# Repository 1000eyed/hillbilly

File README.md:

# hillbilly
This a work in progress repository of a hillbilly keyboard.

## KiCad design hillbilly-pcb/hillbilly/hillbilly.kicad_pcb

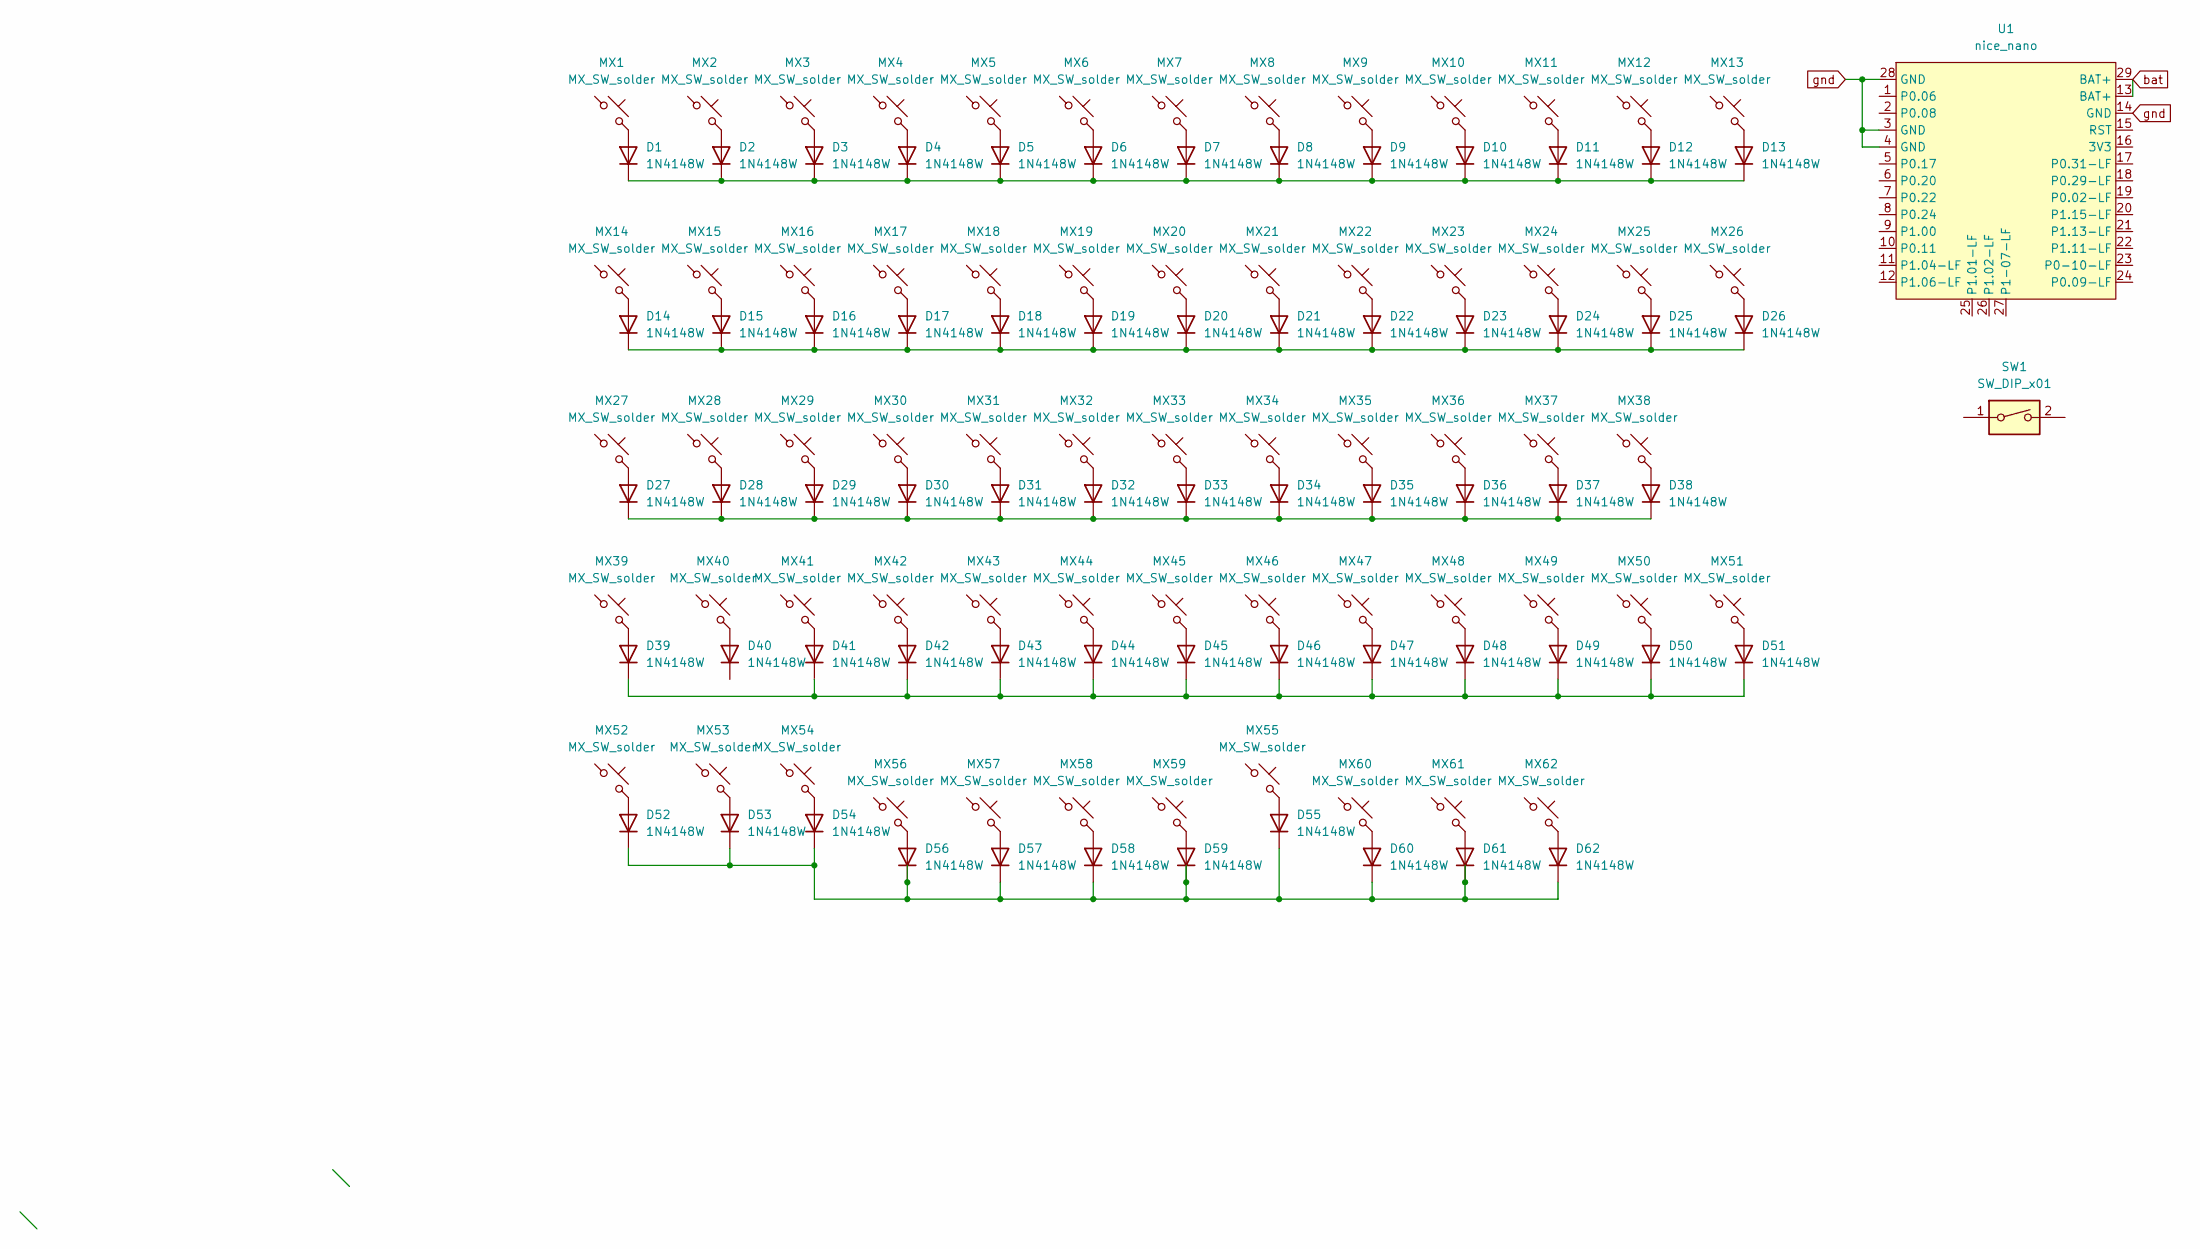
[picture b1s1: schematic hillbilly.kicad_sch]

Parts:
D1, D2, D3, D4, D5, D6, D7, D8, D9, D10, D11, D12, D13, D14, D15, D16, D17, D18, D19, D20, D21, D22, D23, D24, D25, D26, D27, D28, D29, D30, D31, D32, D33, D34, D35, D36, D37, D38, D39, D40, D41, D42, D43, D44, D45, D46, D47, D48, D49, D50, D51, D52, D53, D54, D55, D56, D57, D58, D59, D60, D61, D62: 1N4148W; D_SOD-123
MX1, MX2, MX3, MX4, MX5, MX6, MX7, MX8, MX9, MX10, MX11, MX15, MX16, MX17, MX18, MX19, MX20, MX21, MX22, MX23, MX24, MX28, MX29, MX30, MX31, MX32, MX33, MX34, MX35, MX36, MX37, MX40, MX41, MX42, MX43, MX44, MX45, MX46, MX47, MX48, MX49, MX50, MX51, MX56, MX59, MX60, MX61, MX62: MX_SW_solder; SW_MX_HS_1u
MX12: MX_SW_solder; SW_MX_1u_1.5u_2u
MX13, MX26: MX_SW_solder; SW_MX_1u
MX14: MX_SW_solder; SW_MX_HS_1.5u
MX25: MX_SW_solder; SW_MX_1u_2u_ISO
MX27: MX_SW_solder; SW_MX_HS_1.75u+1.25u_stepped_caps
MX38: MX_SW_solder; SW_MX_HS_1.75u
MX39: MX_SW_solder; SW_MX_HS_1u_2u
MX52, MX53, MX54, MX55: MX_SW_solder; SW_MX_HS_1.25u
MX57: MX_SW_solder; SW_MX_HS_2.75u_1.75u
MX58: MX_SW_solder; SW_MX_HS_1.75u_2.75u
SW1: SW_DIP_x01
U1: nice_nano; nice_nano_AH_USBup

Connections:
unnamed: D1.2 (A), MX1.2
unnamed: D1.1 (K), D2.1 (K), D3.1 (K), D4.1 (K), D5.1 (K), D6.1 (K), D7.1 (K), D8.1 (K), D9.1 (K), D10.1 (K), D11.1 (K), D12.1 (K), D13.1 (K)
unnamed: D2.2 (A), MX2.2
unnamed: D3.2 (A), MX3.2
unnamed: D4.2 (A), MX4.2
unnamed: D5.2 (A), MX5.2
unnamed: D6.2 (A), MX6.2
unnamed: D7.2 (A), MX7.2
unnamed: D8.2 (A), MX8.2
unnamed: D9.2 (A), MX9.2
unnamed: D10.2 (A), MX10.2
unnamed: D11.2 (A), MX11.2
unnamed: D12.2 (A), MX12.2
unnamed: D13.2 (A), MX13.2
unnamed: D14.2 (A), MX14.2
unnamed: D14.1 (K), D15.1 (K), D16.1 (K), D17.1 (K), D18.1 (K), D19.1 (K), D20.1 (K), D21.1 (K), D22.1 (K), D23.1 (K), D24.1 (K), D25.1 (K), D26.1 (K)
unnamed: D15.2 (A), MX15.2
unnamed: D16.2 (A), MX16.2
unnamed: D17.2 (A), MX17.2
unnamed: D18.2 (A), MX18.2
unnamed: D19.2 (A), MX19.2
unnamed: D20.2 (A), MX20.2
unnamed: D21.2 (A), MX21.2
unnamed: D22.2 (A), MX22.2
unnamed: D23.2 (A), MX23.2
unnamed: D24.2 (A), MX24.2
unnamed: D25.2 (A), MX25.2
unnamed: D26.2 (A), MX26.2
unnamed: D27.2 (A), MX27.2
unnamed: D27.1 (K), D28.1 (K), D29.1 (K), D30.1 (K), D31.1 (K), D32.1 (K), D33.1 (K), D34.1 (K), D35.1 (K), D36.1 (K), D37.1 (K), D38.1 (K)
unnamed: D28.2 (A), MX28.2
unnamed: D29.2 (A), MX29.2
unnamed: D30.2 (A), MX30.2
unnamed: D31.2 (A), MX31.2
unnamed: D32.2 (A), MX32.2
unnamed: D33.2 (A), MX33.2
unnamed: D34.2 (A), MX34.2
unnamed: D35.2 (A), MX35.2
unnamed: D36.2 (A), MX36.2
unnamed: D37.2 (A), MX37.2
unnamed: D38.2 (A), MX38.2
unnamed: D39.2 (A), MX39.2
unnamed: D39.1 (K), D41.1 (K), D42.1 (K), D43.1 (K), D44.1 (K), D45.1 (K), D46.1 (K), D47.1 (K), D48.1 (K), D49.1 (K), D50.1 (K), D51.1 (K)
unnamed: D40.2 (A), MX40.2
unnamed: D41.2 (A), MX41.2
unnamed: D42.2 (A), MX42.2
unnamed: D43.2 (A), MX43.2
unnamed: D44.2 (A), MX44.2
unnamed: D45.2 (A), MX45.2
unnamed: D46.2 (A), MX46.2
unnamed: D47.2 (A), MX47.2
unnamed: D48.2 (A), MX48.2
unnamed: D49.2 (A), MX49.2
unnamed: D50.2 (A), MX50.2
unnamed: D51.2 (A), MX51.2
unnamed: D52.2 (A), MX52.2
unnamed: D52.1 (K), D53.1 (K), D54.1 (K), D55.1 (K), D56.1 (K), D57.1 (K), D58.1 (K), D59.1 (K), D60.1 (K), D61.1 (K), D62.1 (K)
unnamed: D53.2 (A), MX53.2
unnamed: D54.2 (A), MX54.2
unnamed: D55.2 (A), MX55.2
unnamed: D56.2 (A), MX56.2
unnamed: D57.2 (A), MX57.2
unnamed: D58.2 (A), MX58.2
unnamed: D59.2 (A), MX59.2
unnamed: D60.2 (A), MX60.2
unnamed: D61.2 (A), MX61.2
unnamed: D62.2 (A), MX62.2
bat: U1.13 (BAT+), U1.29 (BAT+)
gnd: U1.3 (GND), U1.4 (GND), U1.14 (GND), U1.28 (GND)

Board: 2 copper layers, 125 parts (117 on the bottom side), 69 nets, no tracks yet.

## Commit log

2023-08-30 WIP: arrange switch and diode footprints
